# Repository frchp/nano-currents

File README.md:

# NanoCurrents
Spy power consumption.

## Repository

This repository combines hardware and software files for my power consumption projects.

## Hardware

Hardware files for :
  - [NanoCurrents](hw/NanoCurrents_v2.pdf), a way to amplify easily with a small board currents from the nA range, using a INA211 shunt monitor and multiple shunt footprint to use.
  - [NanoCurrents4USB](hw/NanoCurrents4USB.pdf), a way to monitor power consumption on an USB bus, with an integrated STM32L011F4Px microcontroller to measure and send measures via UART. Based on an INA211 shunt monitor, and a basic voltage buffer (ratio 1/2).
  - [NanoCurrentsSupply](hw/NanoCurrentsSupply.pdf), a way to supply three differents voltage to a target and monitor the power consumption (INA240) with the integrated ADC (ADS1015).

## Software

Software for NanoCurrents4USB :
  - Firmware to run on STM32L011F4Px : acquire data and send it via UART.
  - Python script to get UART from COM port on computer and display data in real time.

## Doc

Interesting documentation for power consumption and side power analysis:
 - [Texas Instruments documentation on low side current measurement](doc/AN_texas_Low-Side%20Current%20Sense%20Circuit%20Integration.pdf)
 - [Paper on side power analysis methodology](doc/introduction_to_differential_power_analysis.pdf)
 - [STM32 Reference manual](doc/rm0377-ultralowpower-stm32l0x1-advanced-armbased-32bit-mcus-stmicroelectronics.pdf) and [STM32 datasheet](doc/stm32l011f4.pdf)
 - [Methodology to chose resistor based on DUT](doc/testing_methodology_for_side_channel_resistance_validation.pdf)

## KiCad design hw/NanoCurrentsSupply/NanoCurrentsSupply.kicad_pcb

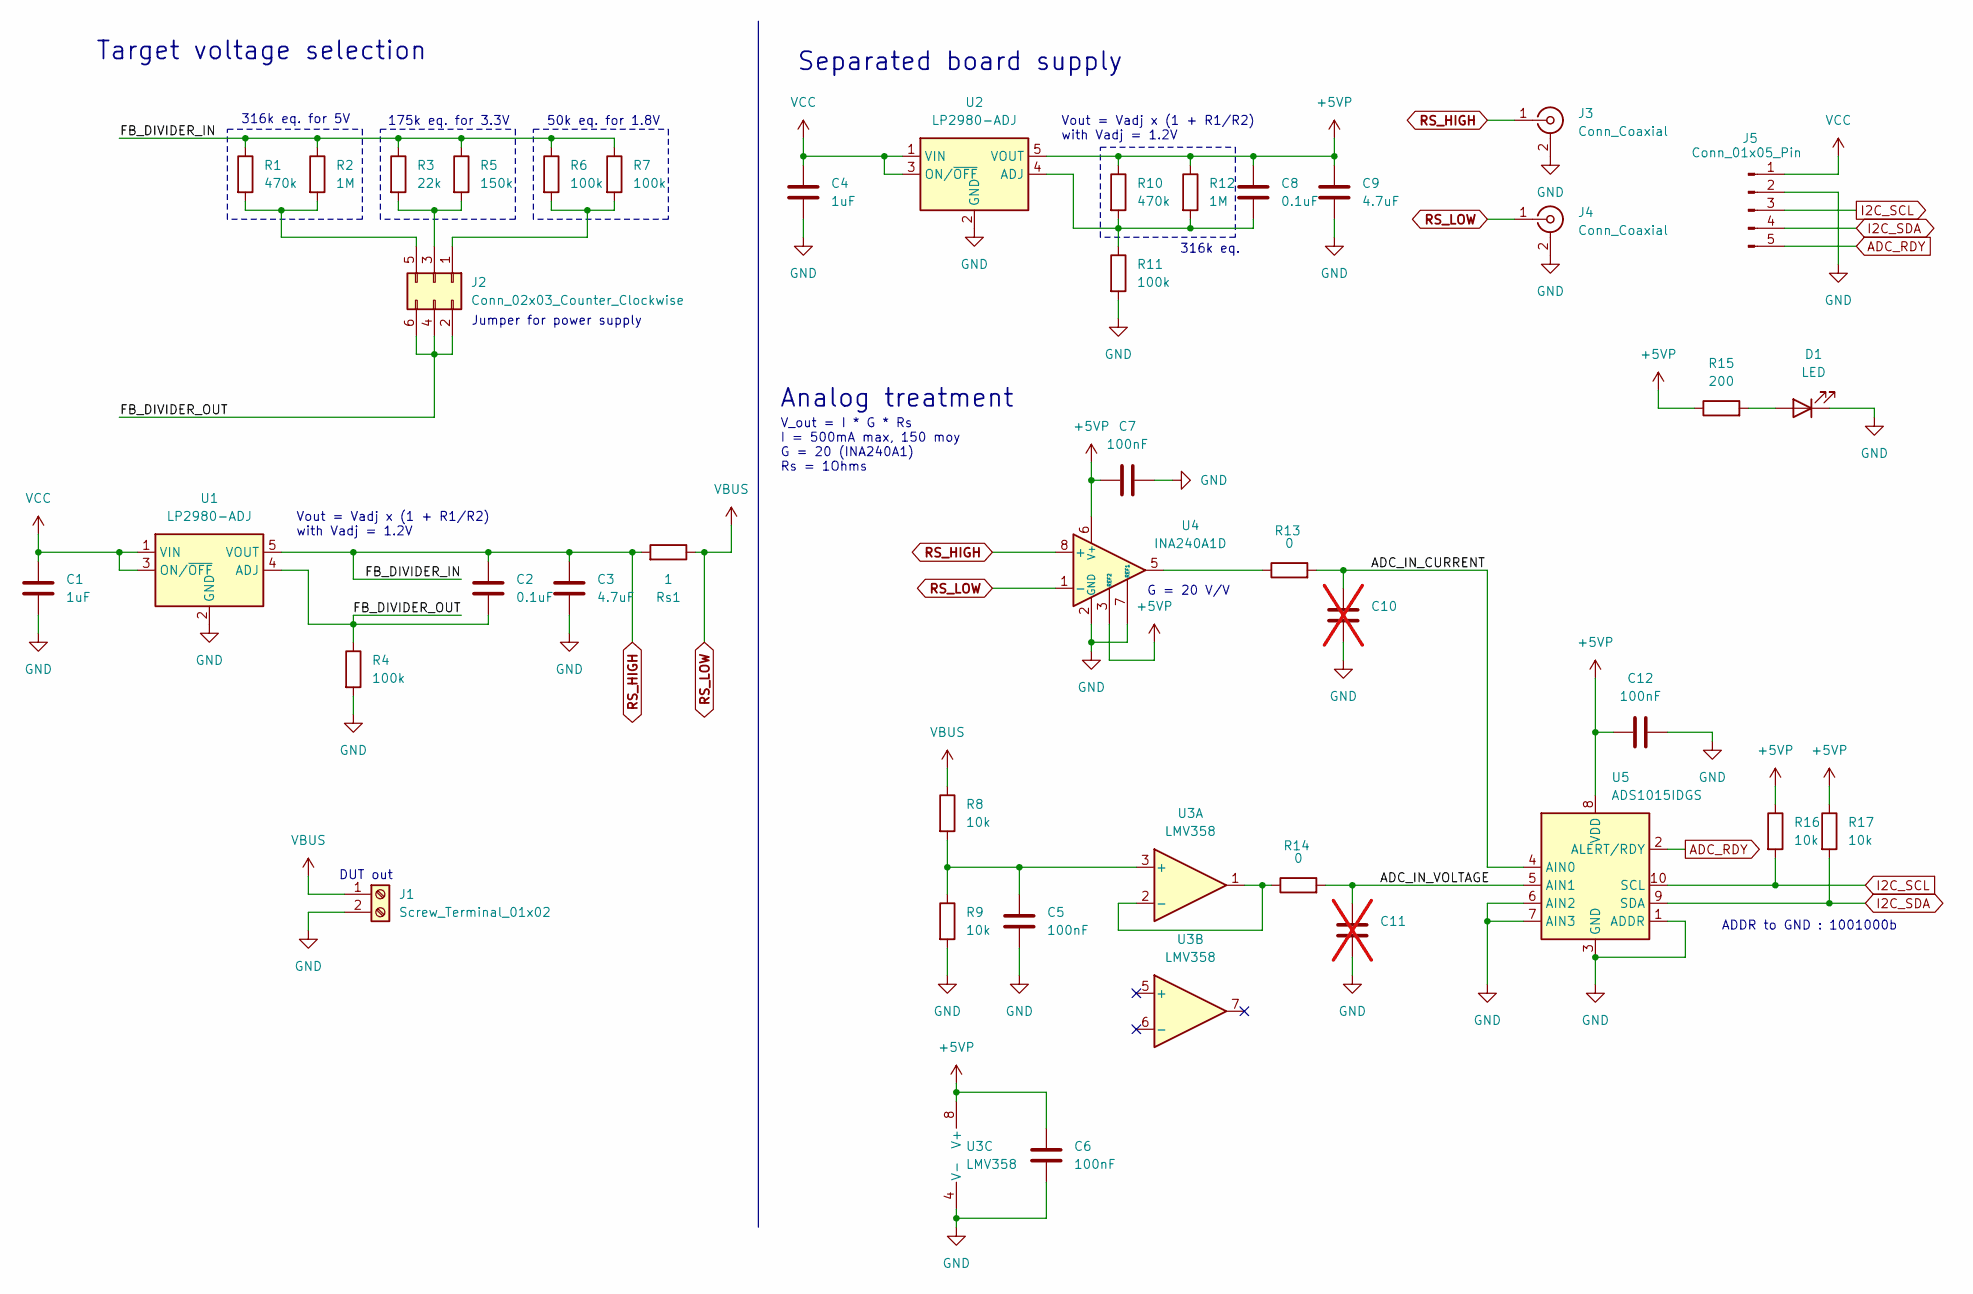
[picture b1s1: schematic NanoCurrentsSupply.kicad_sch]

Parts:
C1, C4: 1uF; C_0603_1608Metric_Pad1.08x0.95mm_HandSolder
C2, C8: 0.1uF; C_0603_1608Metric_Pad1.08x0.95mm_HandSolder
C3, C9: 4.7uF; C_0603_1608Metric_Pad1.08x0.95mm_HandSolder
C5, C6, C7, C12: 100nF; C_0603_1608Metric_Pad1.08x0.95mm_HandSolder
C10, C11: C_0603_1608Metric_Pad1.08x0.95mm_HandSolder; not fitted
D1: LED; LED_0603_1608Metric
J1: Screw_Terminal_01x02; TerminalBlock_bornier-2_P5.08mm
J2: Conn_02x03_Counter_Clockwise; PinSocket_2x03_P2.54mm_Vertical
J3, J4: Conn_Coaxial; SMA_Amphenol_132289_EdgeMount
J5: Conn_01x05_Pin; PinHeader_1x05_P2.54mm_Vertical
R1, R10: 470k; R_0603_1608Metric_Pad0.98x0.95mm_HandSolder
R2, R12: 1M; R_0603_1608Metric_Pad0.98x0.95mm_HandSolder
R3: 22k; R_0603_1608Metric_Pad0.98x0.95mm_HandSolder
R4, R6, R7, R11: 100k; R_0603_1608Metric_Pad0.98x0.95mm_HandSolder
R5: 150k; R_0603_1608Metric_Pad0.98x0.95mm_HandSolder
R8, R9, R16, R17: 10k; R_0603_1608Metric_Pad0.98x0.95mm_HandSolder
R13, R14: 0; R_0603_1608Metric_Pad0.98x0.95mm_HandSolder
R15: 200; R_0603_1608Metric_Pad0.98x0.95mm_HandSolder
Rs1: 1; R_1206_3216Metric_Pad1.30x1.75mm_HandSolder
U1, U2: LP2980-ADJ; SOT-23-5
U3: LMV358; SOIC-8_3.9x4.9mm_P1.27mm
U4: INA240A1D; SOIC-8_3.9x4.9mm_P1.27mm
U5: ADS1015IDGS; TSSOP-10_3x3mm_P0.5mm

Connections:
+5VP: C6.2, C7.1, C8.1, C9.1, C12.1, R10.1, R12.1, R15.1, R16.1, R17.1, U2.5 (VOUT), U3.8 (V+), U4.3 (REF2), U4.6 (V+), U5.8 (VDD)
/ADC_IN_CURRENT: C10.2, R13.2, U5.4 (AIN0)
/ADC_IN_VOLTAGE: C11.2, R14.2, U5.5 (AIN1)
/FB_DIVIDER_OUT: C2.2, J2.2, J2.4, J2.6, R4.1, U1.4 (ADJ)
ADC_RDY: J5.5, U5.2 (ALERT/RDY)
GND: C1.2, C3.2, C4.2, C5.1, C6.1, C7.2, C9.2, C10.1, C11.1, C12.2, D1.1 (K), J1.2, J3.2 (Ext), J4.2 (Ext), J5.2, R4.2, R9.2, R11.2, U1.2 (GND), U2.2 (GND), U3.4 (V-), U4.2 (GND), U4.4 (GND), U4.7 (REF1), U5.1 (ADDR), U5.3 (GND), U5.6 (AIN2), U5.7 (AIN3)
I2C_SCL: J5.3, R16.2, U5.10 (SCL)
I2C_SDA: J5.4, R17.2, U5.9 (SDA)
unnamed: D1.2 (A), R15.2
unnamed: J2.1, R6.2, R7.2
unnamed: J2.3, R3.2, R5.2
unnamed: J2.5, R1.2, R2.2
unnamed: R13.1, U4.5
unnamed: C8.2, R10.2, R11.1, R12.2, U2.4 (ADJ)
unnamed: C5.2, R8.2, R9.1, U3.3 (+)
unnamed: R14.1, U3.1, U3.2 (-)
RS_HIGH: C2.1, C3.1, J3.1 (In), R1.1, R2.1, R3.1, R5.1, R6.1, R7.1, Rs1.2, U1.5 (VOUT), U4.8 (+)
RS_LOW: J1.1, J4.1 (In), R8.1, Rs1.1, U4.1 (-)
VCC: C1.1, C4.1, J5.1, U1.1 (VIN), U1.3 (ON/~OFF), U2.1 (VIN), U2.3 (ON/~OFF)

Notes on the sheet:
Target voltage selection
50k eq. for 1.8V
Vout = Vadj x (1 + R1/R2) with Vadj = 1.2V
175k eq. for 3.3V
V_out = I * G * Rs I = 500mA max, 150 moy G = 20 (INA240A1) Rs = 1Ohms
DUT out
ADDR to GND : 1001000b
Analog treatment
Jumper for power supply
G = 20 V/V
Separated board supply
316k eq. for 5V
316k eq.

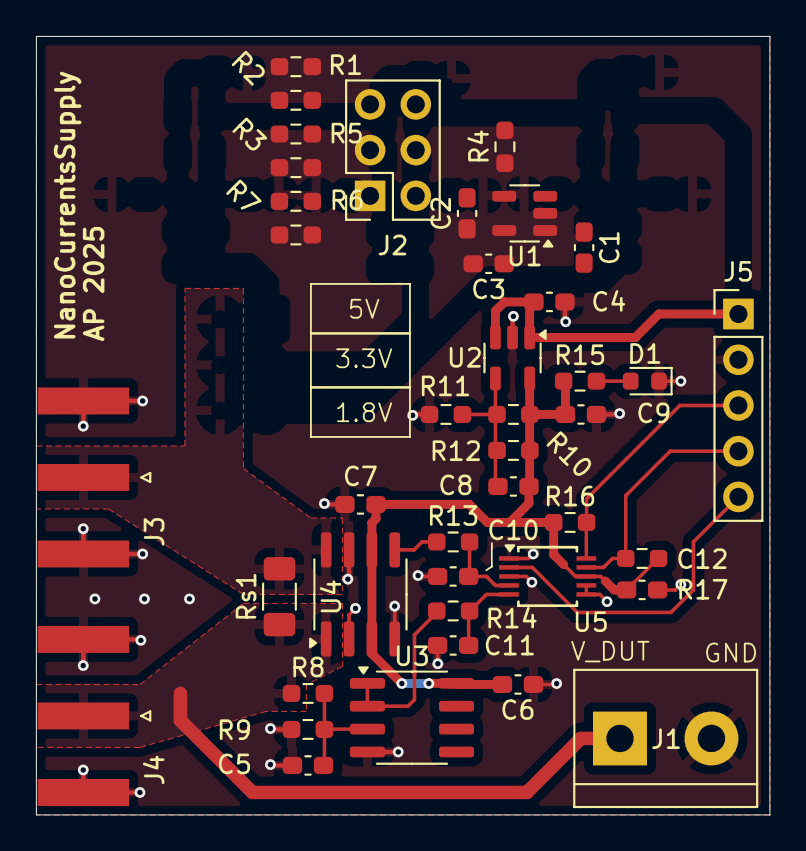
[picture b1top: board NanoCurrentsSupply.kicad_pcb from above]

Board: 2 copper layers, 40.8 x 43.2 mm, 41 parts (0 on the bottom side), 19 nets.

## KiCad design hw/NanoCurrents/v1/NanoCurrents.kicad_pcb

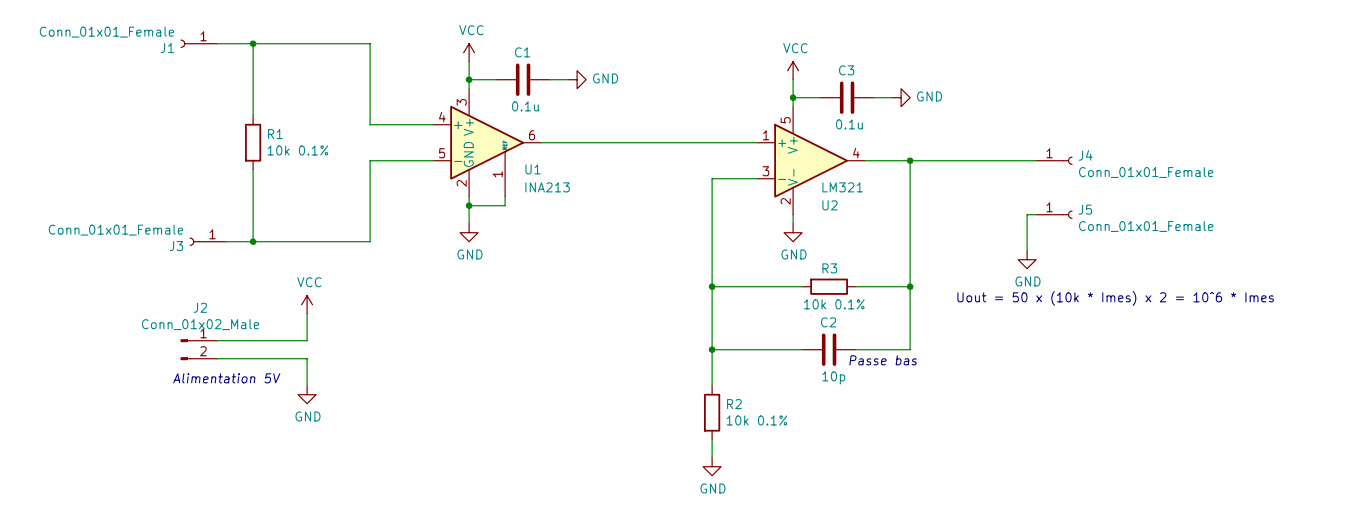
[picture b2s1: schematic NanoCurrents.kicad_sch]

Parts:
C1, C3: 0.1u; C_0805_2012Metric
C2: 10p; C_0805_2012Metric
J1, J3, J4, J5: Conn_01x01_Female; SolderWirePad_1x01_SMD_5x10mm
J2: Conn_01x02_Male; PinHeader_1x02_P2.54mm_Vertical
R1, R2, R3: 10k 0.1%; R_0805_2012Metric
U1: INA213; SC-70-6
U2: LM321; SOT-23-5

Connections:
GND: C1.2, C3.2, J2.2, J5.1, R2.2, U1.1 (REF), U1.2 (GND), U2.2 (V-)
unnamed: C2.1, R2.1, R3.2, U2.3 (-)
unnamed: C2.2, J4.1, R3.1, U2.4
unnamed: J1.1, R1.1, U1.4 (+)
unnamed: J3.1, R1.2, U1.5 (-)
unnamed: U1.6, U2.1 (+)
VCC: C1.1, C3.1, J2.1, U1.3 (V+), U2.5 (V+)

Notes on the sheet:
Passe bas
Alimentation 5V
Uout = 50 x (10k * Imes) x 2 = 10^6 * Imes

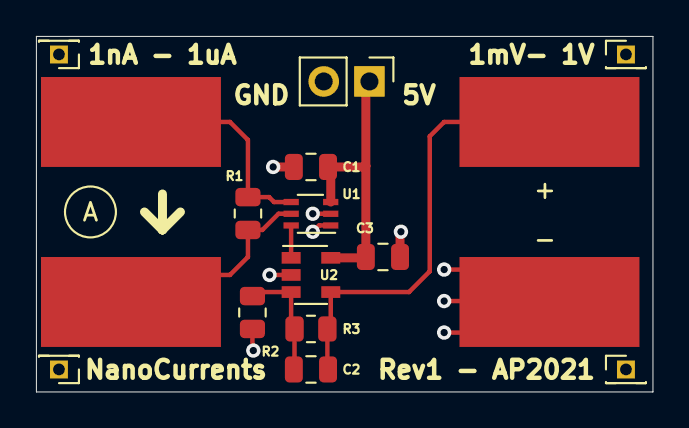
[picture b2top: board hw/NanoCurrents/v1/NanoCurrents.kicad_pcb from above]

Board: 2 copper layers, 34.2 x 19.8 mm, 13 parts (0 on the bottom side), 7 nets.

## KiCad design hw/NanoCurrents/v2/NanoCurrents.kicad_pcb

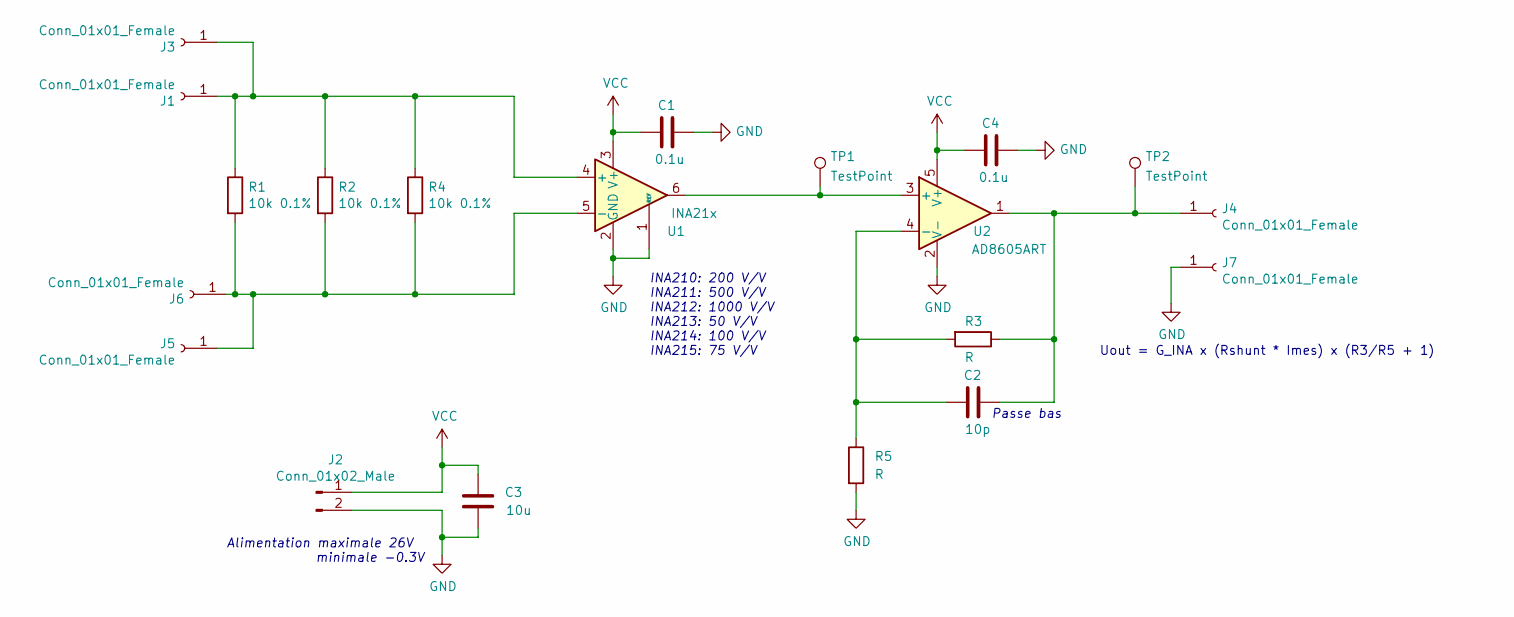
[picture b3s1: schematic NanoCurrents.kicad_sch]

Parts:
C1, C4: 0.1u; C_0603_1608Metric_Pad1.08x0.95mm_HandSolder
C2: 10p; C_0603_1608Metric_Pad1.08x0.95mm_HandSolder
C3: 10u; C_0805_2012Metric
J1, J6: Conn_01x01_Female; MountingHole_2.2mm_M2_Pad_Via
J2: Conn_01x02_Male; PinHeader_1x02_P2.54mm_Vertical
J3, J4, J5, J7: Conn_01x01_Female; PinHeader_1x01_P2.54mm_Vertical
R1: 10k 0.1%; R_2512_6332Metric_Pad1.40x3.35mm_HandSolder
R2: 10k 0.1%; R_1206_3216Metric_Pad1.30x1.75mm_HandSolder
R3, R5: R; R_0603_1608Metric_Pad0.98x0.95mm_HandSolder
R4: 10k 0.1%; R_0805_2012Metric
TP1, TP2: TestPoint; TestPoint_Pad_D1.0mm
U1: INA21x; SC-70-6
U2: AD8605ART; SOT-23-5_HandSoldering

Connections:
GND: C1.2, C3.1, C4.2, J2.2, J7.1, R5.2, U1.1 (REF), U1.2 (GND), U2.2 (V-)
unnamed: C2.1, R3.2, R5.1, U2.4 (-)
unnamed: C2.2, J4.1, R3.1, TP2.1, U2.1
unnamed: J1.1, J3.1, R1.1, R2.1, R4.1, U1.4 (+)
unnamed: J5.1, J6.1, R1.2, R2.2, R4.2, U1.5 (-)
unnamed: TP1.1, U1.6, U2.3 (+)
VCC: C1.1, C3.2, C4.1, J2.1, U1.3 (V+), U2.5 (V+)

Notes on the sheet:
Passe bas
Alimentation maximale 26V minimale -0.3V
INA210: 200 V/V INA211: 500 V/V INA212: 1000 V/V INA213: 50 V/V INA214: 100 V/V INA215: 75 V/V
Uout = G_INA x (Rshunt * Imes) x (R3/R5 + 1)

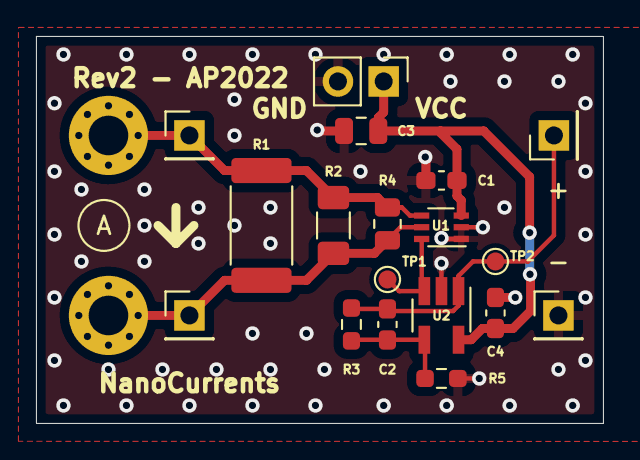
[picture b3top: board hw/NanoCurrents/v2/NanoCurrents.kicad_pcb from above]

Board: 2 copper layers, 31.5 x 21.5 mm, 20 parts (0 on the bottom side), 7 nets.

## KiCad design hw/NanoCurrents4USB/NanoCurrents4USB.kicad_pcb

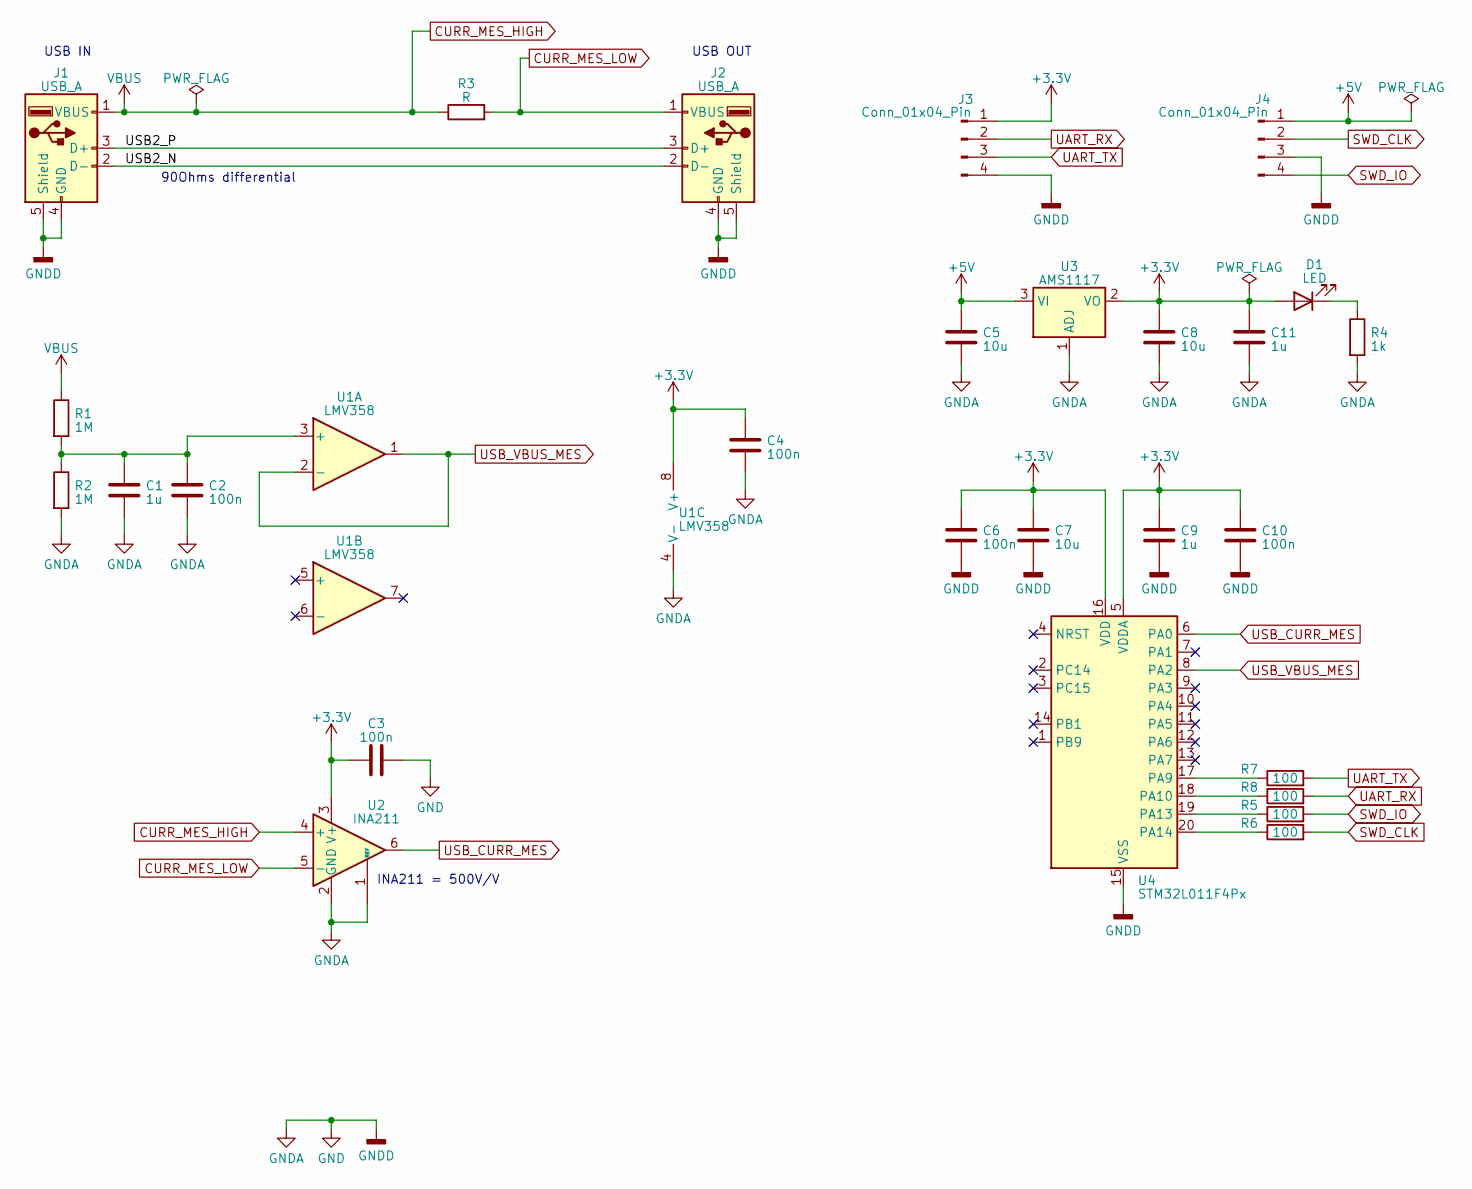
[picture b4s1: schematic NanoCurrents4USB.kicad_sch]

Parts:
C1, C9, C11: 1u; C_0805_2012Metric_Pad1.18x1.45mm_HandSolder
C2, C3, C4, C6, C10: 100n; C_0603_1608Metric_Pad1.08x0.95mm_HandSolder
C5, C7, C8: 10u; C_0805_2012Metric_Pad1.18x1.45mm_HandSolder
D1: LED; D_0805_2012Metric_Pad1.15x1.40mm_HandSolder
J1, J2: USB_A; USB_A_CONNFLY_DS1095-WNR0
J3, J4: Conn_01x04_Pin; PinHeader_1x04_P2.54mm_Vertical
R1, R2: 1M; R_0603_1608Metric_Pad0.98x0.95mm_HandSolder
R3: R; R_0805_2012Metric_Pad1.20x1.40mm_HandSolder
R4: 1k; R_0603_1608Metric_Pad0.98x0.95mm_HandSolder
R5, R6, R7, R8: 100; R_0603_1608Metric_Pad0.98x0.95mm_HandSolder
U1: LMV358; TSSOP-8_3x3mm_P0.65mm
U2: INA211; SOT-363_SC-70-6_Handsoldering
U3: AMS1117; SOT-223-3_TabPin2
U4: STM32L011F4Px; TSSOP-20_4.4x6.5mm_P0.65mm

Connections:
+3.3V: C3.1, C4.1, C6.1, C7.1, C8.1, C9.1, C10.1, C11.1, D1.2 (A), J3.1, U1.8 (V+), U2.3 (V+), U3.2 (VO), U4.5 (VDDA), U4.16 (VDD)
+5V: C5.1, J4.1, U3.3 (VI)
/USB2_N: J1.2 (D-), J2.2 (D-)
/USB2_P: J1.3 (D+), J2.3 (D+)
CURR_MES_HIGH: J1.1 (VBUS), R1.1, R3.1, U2.4 (+)
CURR_MES_LOW: J2.1 (VBUS), R3.2, U2.5 (-)
GND: C1.2, C2.2, C3.2, C4.2, C5.2, C6.2, C7.2, C8.2, C9.2, C10.2, C11.2, J1.4 (GND), J1.5 (Shield), J2.4 (GND), J2.5 (Shield), J3.4, J4.3, R2.2, R4.2, U1.4 (V-), U2.1 (REF), U2.2 (GND), U3.1 (ADJ), U4.15 (VSS)
unnamed: D1.1 (K), R4.1
unnamed: C1.1, C2.1, R1.2, R2.1, U1.3 (+)
unnamed: R7.1, U4.17 (PA9)
unnamed: R8.1, U4.18 (PA10)
unnamed: R5.1, U4.19 (PA13)
unnamed: R6.1, U4.20 (PA14)
SWD_CLK: J4.2, R6.2
SWD_IO: J4.4, R5.2
UART_RX: J3.2, R8.2
UART_TX: J3.3, R7.2
USB_CURR_MES: U2.6, U4.6 (PA0)
USB_VBUS_MES: U1.1, U1.2 (-), U4.8 (PA2)

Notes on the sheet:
INA211 = 500V/V
USB IN
90Ohms differential
USB OUT

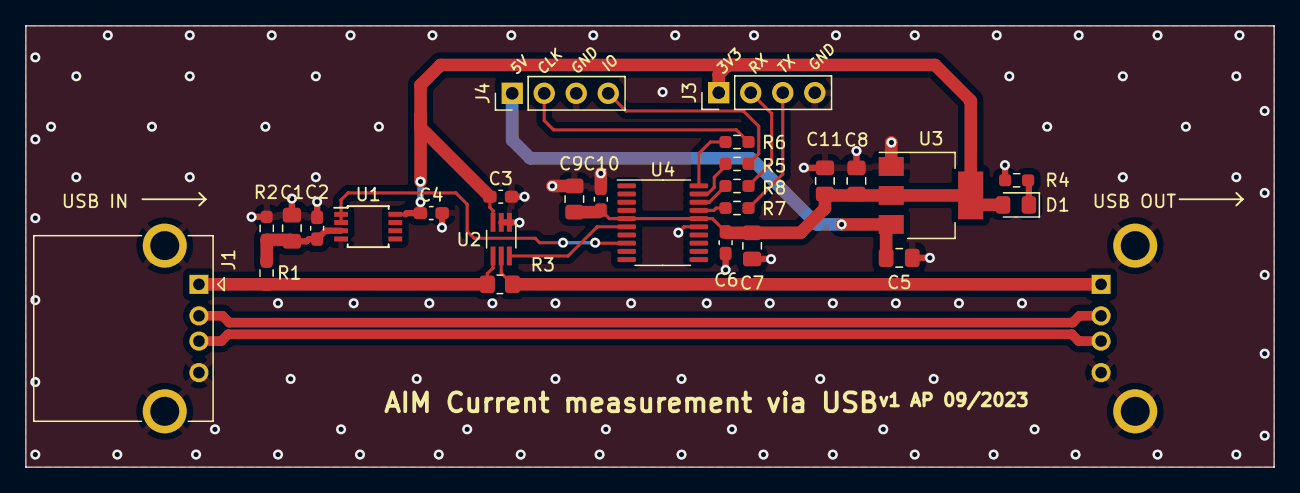
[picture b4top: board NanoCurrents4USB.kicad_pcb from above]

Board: 2 copper layers, 99.0 x 35.0 mm, 28 parts (1 on the bottom side), 19 nets.

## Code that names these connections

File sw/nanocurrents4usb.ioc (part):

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Mcu.Name=STM32L011F(3-4)Px
Mcu.Package=TSSOP20
Mcu.UserName=STM32L011F4Px
PA0-CK_IN.Mode=IN0
PA0-CK_IN.Signal=ADC_IN0
PA1.Mode=IN1
PA1.Signal=ADC_IN1
PA10.Mode=Asynchronous
PA10.Signal=USART2_RX
PA13.Mode=Serial_Wire
PA13.Signal=SYS_SWDIO
PA14.Mode=Serial_Wire
PA14.Signal=SYS_SWCLK
PA9.Mode=Asynchronous
PA9.Signal=USART2_TX
RCC.HSE_VALUE=8000000
RCC.SYSCLKFreq_VALUE=2097000
board=custom

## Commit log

2025-02-07 Add HW files and doc, add base STCube project for prototyping
2025-02-10 Start ADC and send measurements via UART
2025-02-14 Update ST project to use timer
2025-02-14 Add standalone project to save memory
2025-02-14 Remove STCube project
2025-02-14 First standalone implementation
2025-02-14 Application is functionnal Use CubeIDE for debug, VSCode is glitching
2025-02-14 Remove build files
2025-02-14 Add gitignore
2025-02-15 Voltage is on PA2 not PA1
2025-02-16 !fix DMA transfer cfg
2025-02-17 Misc
2025-02-17 Add conversion for UART output
2025-02-17 Rework transmission to not be blocking
2025-02-17 Add padding to uart packet in case of future modifications
2025-02-17 Pack values
2025-02-17 Make global variables static
2025-02-18 Add CRC to message
2025-02-18 Reorganize files + fix shunt value + add cfg to chose between raw and computed
2025-02-18 Create display_data.py
    Read incoming UART data and display it
2025-02-18 Add start byte to ease decoding
2025-02-18 Compute data in python
2025-02-18 Add python test file to emulate data
2025-02-18 Increase refresh rate graph
2025-02-19 Add gitignore for HW files
2025-02-19 Add some documentation and prepare for next HW
2025-02-19 NanoCurrentsSupplySchematic done, draft of PCB done
2025-02-19 Finished first PCB of NanoCurrentsSupply
2025-02-19 Update HW before production
2025-02-19 Rev B00 : only use one regulator
2025-02-20 Remove boolean dependency
2025-02-21 !fix CRC computation on STM32 + UART send at the same time + timing of enabling TXE interrupt
2025-02-21 Revert debug code
